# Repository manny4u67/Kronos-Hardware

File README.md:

# Kronos Hardware
 Kronos - By AddeyX

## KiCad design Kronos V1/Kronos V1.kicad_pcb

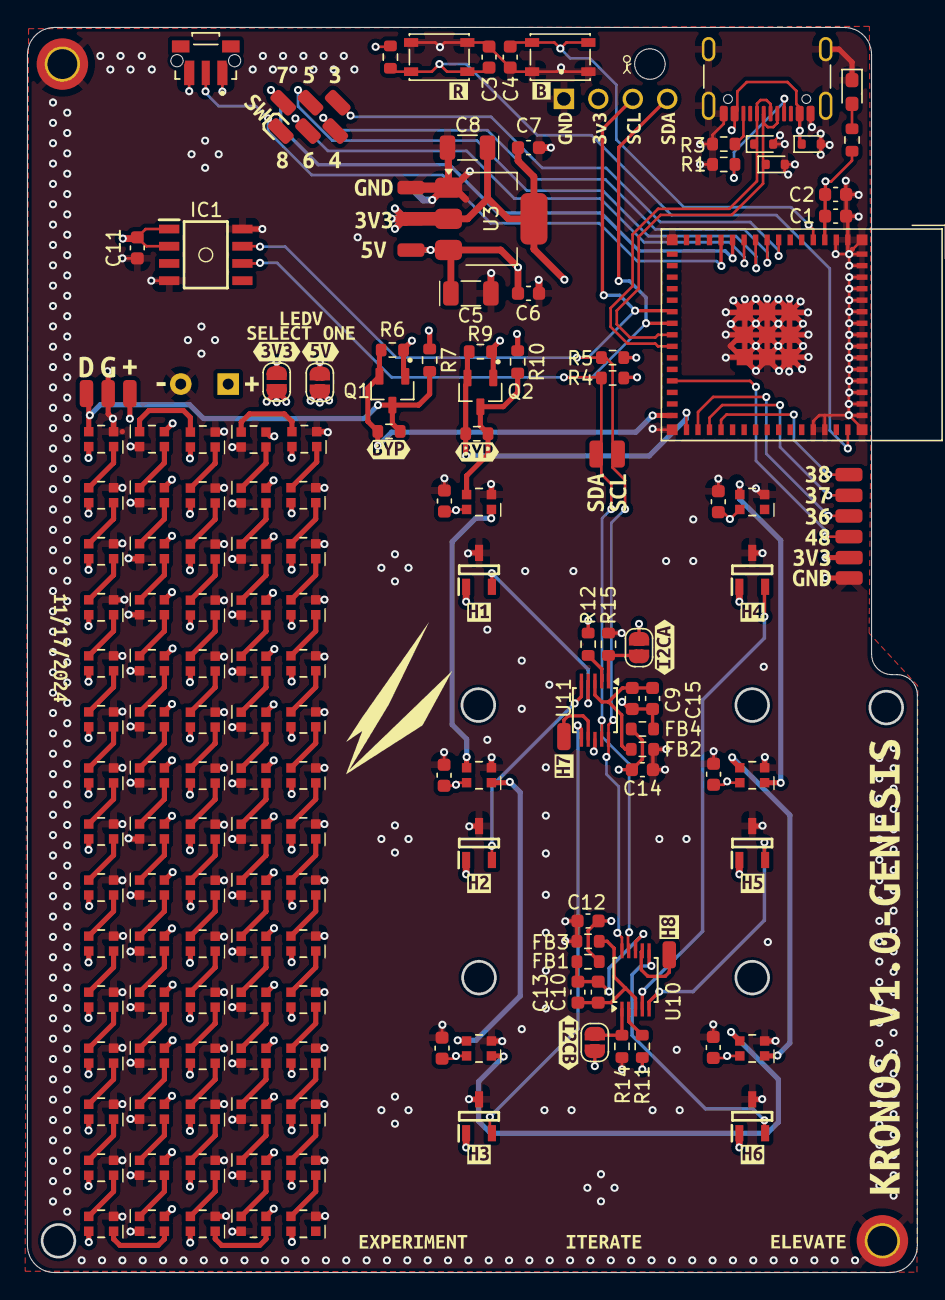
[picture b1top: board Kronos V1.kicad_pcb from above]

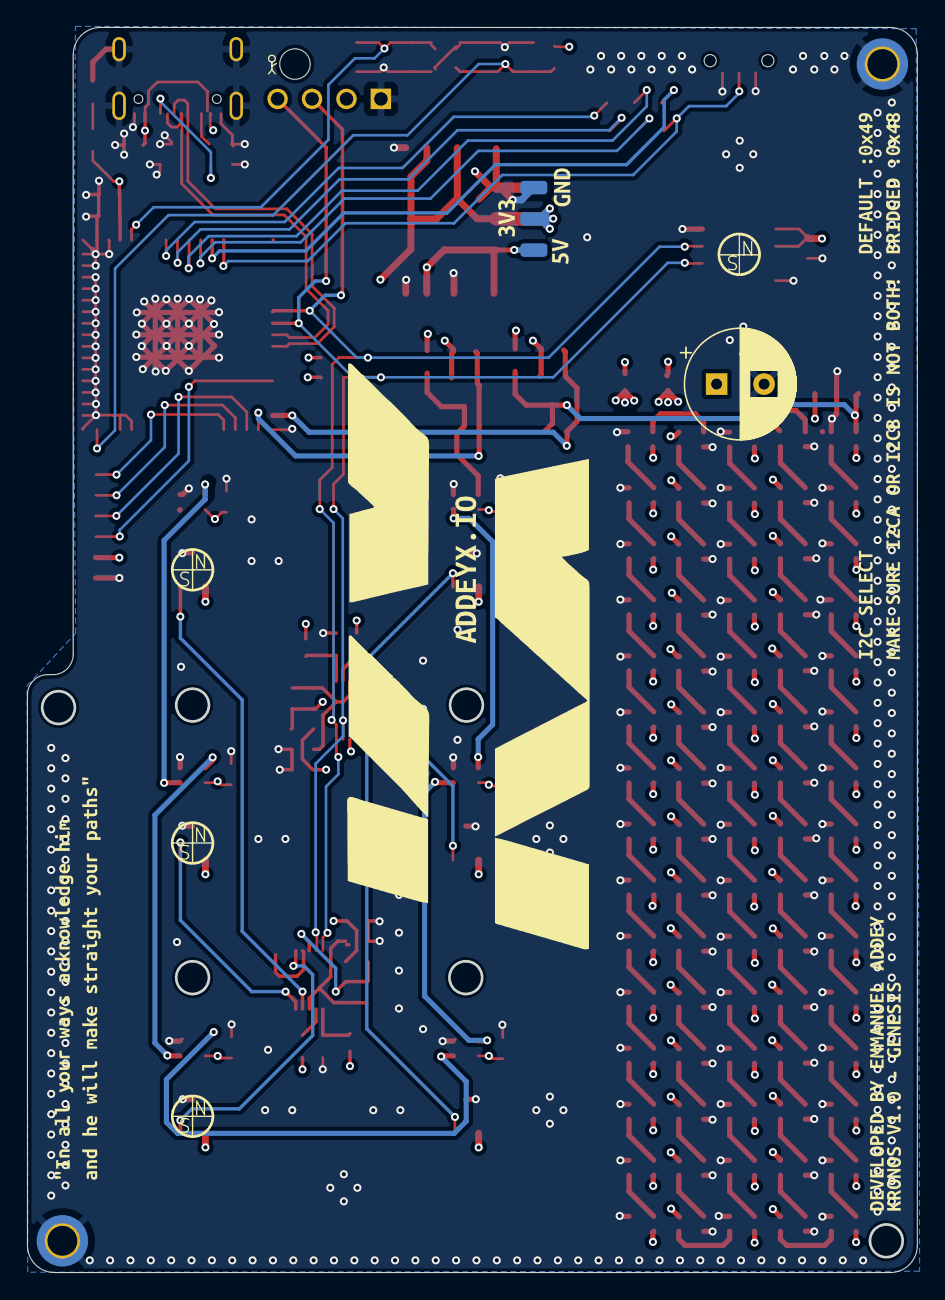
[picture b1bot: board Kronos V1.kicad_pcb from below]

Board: 4 copper layers, 65.6 x 91.8 mm, 229 parts (12 on the bottom side), 122 nets.

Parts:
BOOT1: SW_SPST_PTS810
C1, C3, C4, C92, C93, C94, C95, C96, C97: 0.1uF; C_0603_1608Metric
C2, C9, C10, C12, C14: 10uF; C_0603_1608Metric
C5, C8: 22uF; C_1206_3216Metric
C6, C7, C11, C13, C15: 100nf; C_0603_1608Metric
C17: C_Polarized_US; CP_Radial_D8.0mm_P3.50mm
D1, D2, D3: TPD1E10B06; D_SOD-523
D4: LED; LED_0603_1608Metric_Pad1.05x0.95mm_HandSolder
FB1, FB2, FB3, FB4: FerriteBead_Small; R_0603_1608Metric
H1, H2: MountingHole_Pad; MountingHole_2.2mm_M2_DIN965_Pad_TopBottom
IC1: AS5600-ASOT; AS5600_SOIC127P600X175-8N
J1: USB_C_Receptacle_USB2.0_16P; USB_C_Receptacle_GCT_USB4105-xx-A_16P_TopMnt_Horizontal
JP1, JP2, JP3, JP4: SolderJumper_2_Open; SolderJumper-2_P1.3mm_Open_RoundedPad1.0x1.5mm
PD1, PD2, PD3, PD4, PD5, PD6, PD7, PD8, PD9, PD10, PD11, PD12, PD13, PD13#2, PD14, PD14#2, PD14#3, PD14#4, PD15, PD15#2, PD17, PD18, PD19, PD20, PD21: Test_Pad2
Q1, Q2: BSS138; SOT95P240X111-3N
R1, R3, R16: 5.1k; R_0603_1608Metric
R2, R4, R5, R6, R7, R9, R10, R11, R12, R14, R15: 10k; R_0603_1608Metric
R8, R13: 0(JMP); R_0603_1608Metric
RESET1: SW_SPST_PTS810
S1: TL3340AF160QG; SW_TL3340AF160QG
U1: DM-OLED096-636; MODULE_DM-OLED096-636
U2: ESP32-S3-MINI-1; ESP32-S2-MINI-1
U3: AMS1117-3.3; SOT-223-3_TabPin2
U4, U5, U6, U7, U8, U9: AH49ENTR-G1; SOT95P280X145-3N
U10, U11: ADS1115IDGS; TSSOP-10_3x3mm_P0.5mm
U12, U13, U14, U15, U16, U17, U18, U19, U20, U21, U22, U23, U24, U25, U26, U27, U28, U29, U30, U31, U32, U33, U34, U35, U36, U37, U38, U39, U40, U41, U42, U43, U44, U45, U46, U47, U48, U49, U50, U51, U52, U53, U54, U55, U56, U57, U58, U59, U60, U61, U62, U63, U64, U65, U66, U67, U68, U69, U70, U71, U72, U73, U74, U75, U76, U77, U78, U79, U80, U81, U82, U83, U84, U85, U86, U87, U88, U89, U90, U91, U92: WS2812-2020; LED_WS2812-2020
kibuzzard-66F4CFAA: G***; kibuzzard-66F4CFAA
kibuzzard-66FB33A5: G***; kibuzzard-66FB33A5
kibuzzard-66FB339E: G***; kibuzzard-66FB339E
kibuzzard-66FB3378: G***; kibuzzard-66FB3378
kibuzzard-66FCA7D9: G***; kibuzzard-66FCA7D9
kibuzzard-66FCA7E8: G***; kibuzzard-66FCA7E8
kibuzzard-673A4A14: G***; kibuzzard-673A4A14
kibuzzard-673A4A24: G***; kibuzzard-673A4A24
kibuzzard-673A6C08: G***; kibuzzard-673A6C08
kibuzzard-673A37E5: G***; kibuzzard-673A37E5
kibuzzard-673A37ED: G***; kibuzzard-673A37ED
kibuzzard-673A37F5: G***; kibuzzard-673A37F5
kibuzzard-673A52CF: G***; kibuzzard-673A52CF
kibuzzard-673A66C9: G***; kibuzzard-673A66C9
kibuzzard-673A66CE: G***; kibuzzard-673A66CE
kibuzzard-673A66D4: G***; kibuzzard-673A66D4
kibuzzard-673A66D9: G***; kibuzzard-673A66D9
kibuzzard-673A67D1: G***; kibuzzard-673A67D1
kibuzzard-673A367D, kibuzzard-673A367D#2: G***; kibuzzard-673A367D
kibuzzard-673A380C: G***; kibuzzard-673A380C
kibuzzard-673A2861: G***; kibuzzard-673A2861
kibuzzard-673A2872: G***; kibuzzard-673A2872
kibuzzard-673A3813: G***; kibuzzard-673A3813
kibuzzard-673A3819: G***; kibuzzard-673A3819
kibuzzard-673A4853: G***; kibuzzard-673A4853
kibuzzard-673AB92A: G***; kibuzzard-673AB92A
kibuzzard-673BD2C0: G***; kibuzzard-673BD2C0
kibuzzard-673BD08D: G***; kibuzzard-673BD08D
kibuzzard-673BD012: G***; kibuzzard-673BD012
kibuzzard-673BD17F: G***; kibuzzard-673BD17F
kibuzzard-673BD057: G***; kibuzzard-673BD057
kibuzzard-673BDAC6: G***; kibuzzard-673BDAC6
kibuzzard-6736A45D: G***; kibuzzard-6736A45D
kibuzzard-6736A453: G***; kibuzzard-6736A453
kibuzzard-6736AEA1: G***; kibuzzard-6736AEA1
kibuzzard-6736AEA5: G***; kibuzzard-6736AEA5
kibuzzard-6736AEAD: G***; kibuzzard-6736AEAD
kibuzzard-6736AEB1: G***; kibuzzard-6736AEB1
kibuzzard-6736AEBA, kibuzzard-6736AEBA#2, kibuzzard-6736AEBA#3: G***; kibuzzard-6736AEBA
kibuzzard-6736AEC3, kibuzzard-6736AEC3#2, kibuzzard-6736AEC3#3: G***; kibuzzard-6736AEC3
kibuzzard-67368FCC: G***; kibuzzard-67368FCC
kibuzzard-67368FDA: G***; kibuzzard-67368FDA
kibuzzard-673412D5: G***; kibuzzard-673412D5
kibuzzard-673412DD: G***; kibuzzard-673412DD
kibuzzard-66993841: G***; kibuzzard-66993841
kibuzzard-67341636: G***; kibuzzard-67341636
kibuzzard-67341641: G***; kibuzzard-67341641
kibuzzard-67341688: G***; kibuzzard-67341688

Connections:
3V3: C1.1, C2.1, C7.1, C8.1, C11.2, C12.2, C14.2, FB1.1, FB2.1, IC1.1 (VDD5V), IC1.2 (VDD3V3), JP1.1 (A), JP2.1 (A), JP4.2 (B), PD12.1, PD14#3.1, PD14#4.1, Q1.1, Q2.1, R2.1, R4.1, R5.1, R6.1, R9.1, R11.1, R12.1, R16.2, U1.2 (VCC_IN), U2.3 (3V3), U3.2 (VO), U4.1 (VCC), U5.1 (VCC), U6.1 (VCC), U7.1 (VCC), U8.1 (VCC), U9.1 (VCC)
5VUSB: C5.1, C6.2, D1.1 (A1), J1.A4 (VBUS), J1.A9 (VBUS), J1.B4 (VBUS), J1.B9 (VBUS), JP3.1 (A), PD13.1, PD13#2.1, R7.1, R10.1, U3.3 (VI)
/ESP32_EN: C3.1, R2.2, RESET1.3 (K), RESET1.4 (A), U2.45 (EN)
/GPIO0: BOOT1.3 (K), BOOT1.4 (A), C4.1, U2.4 (IO0)
/GPIO3: PD1.1, U2.7 (IO3)
/GPIO4: PD2.1, U2.8 (IO4)
/GPIO5: PD3.1, U2.9 (IO5)
/GPIO6: PD4.1, U2.10 (IO6)
/GPIO7: PD5.1, U2.11 (IO7)
/GPIO8: PD6.1, S1.2, U2.12 (IO8)
/GPIO36: PD7.1, U2.32 (IO36)
/GPIO37: PD8.1, U2.33 (IO37)
/GPIO38: PD9.1, U2.34 (IO38)
/GPIO47: PD10.1, U2.27 (IO47)
/HALLC1R1: U5.2 (OUT), U10.4 (AIN0)
/HALLC1R2: U6.2 (OUT), U10.5 (AIN1)
/HALLC1R3: U8.2 (OUT), U10.6 (AIN2)
/HALLC2R1: U4.2 (OUT), U11.4 (AIN0)
/HALLC2R2: U7.2 (OUT), U11.5 (AIN1)
/HALLC2R3: U9.2 (OUT), U11.6 (AIN2)
/I2C_SCL: IC1.7 (SCL), PD14.1, R5.2, U1.3 (SCL), U2.21 (IO17), U10.10 (SCL), U11.10 (SCL)
/I2C_SDA: IC1.6 (SDA), PD14#2.1, R4.2, U1.4 (SDA), U2.22 (IO18), U10.9 (SDA), U11.9 (SDA)
/USB_N: D3.1 (A1), J1.A7 (D-), J1.B7 (D-), U2.23 (IO19)
/USB_P: D2.1 (A1), J1.A6 (D+), J1.B6 (D+), U2.24 (IO20)
A3V3: C10.2, C13.2, FB1.2, U10.8 (VDD)
A3V3B: C9.2, C15.2, FB2.2, U11.8 (VDD)
AGND: C10.1, C13.1, FB3.2, U10.3 (GND)
AGNDB: C9.1, C15.1, FB4.2, U11.3 (GND)
AUXRGBOUT: PD20.1, Q1.3, R7.2, R8.1, U12.3 (DI)
GND: BOOT1.1, BOOT1.2, C1.2, C2.2, C3.2, C4.2, C5.2, C6.1, C7.2, C8.2, C11.1, C12.1, C14.1, C17.2, C92.2, C93.2, C94.2, C95.2, C96.2, C97.2, D1.2 (A2), D2.2 (A2), D3.2 (A2), D4.1, FB3.1, FB4.1, H1.1, H2.1, IC1.4 (GND), IC1.8 (DIR), J1.A1 (GND), J1.A12 (GND), J1.B1 (GND), J1.B12 (GND), J1.S1 (SHIELD), PD11.1, PD15.1, PD15#2.1, PD21.1, R1.2, R3.2, R14.2, R15.2, RESET1.1, RESET1.2, S1.1, S1.3, U1.1 (GND), U2.1 (GND), U2.2 (GND), U2.42 (GND), U2.43 (GND), U2.46 (GND), U2.47 (GND), U2.48 (GND), U2.49 (GND), U2.50 (GND), U2.51 (GND), U2.52 (GND), U2.53 (GND), U2.54 (GND), U2.55 (GND), U2.56 (GND), U2.57 (GND), U2.58 (GND), U2.59 (GND), U2.60 (GND), U2.61 (GND), U2.62 (GND), U2.63 (GND), U2.64 (GND), U2.65 (GND), U3.1 (GND), U4.3 (GND), U5.3 (GND), U6.3 (GND), U7.3 (GND), U8.3 (GND), U9.3 (GND), U12.2 (GND), U13.2 (GND), U14.2 (GND), U15.2 (GND), U16.2 (GND), U17.2 (GND), U18.2 (GND), U19.2 (GND), U20.2 (GND), U21.2 (GND), U22.2 (GND), U23.2 (GND), U24.2 (GND), U25.2 (GND), U26.2 (GND), U27.2 (GND), U28.2 (GND), U29.2 (GND), U30.2 (GND), U31.2 (GND), U32.2 (GND), U33.2 (GND), U34.2 (GND), U35.2 (GND), U36.2 (GND), U37.2 (GND), U38.2 (GND), U39.2 (GND), U40.2 (GND), U41.2 (GND), U42.2 (GND), U43.2 (GND), U44.2 (GND), U45.2 (GND), U46.2 (GND), U47.2 (GND), U48.2 (GND), U49.2 (GND), U50.2 (GND), U51.2 (GND), U52.2 (GND), U53.2 (GND), U54.2 (GND), U55.2 (GND), U56.2 (GND), U57.2 (GND), U58.2 (GND), U59.2 (GND), U60.2 (GND), U61.2 (GND), U62.2 (GND), U63.2 (GND), U64.2 (GND), U65.2 (GND), U66.2 (GND), U67.2 (GND), U68.2 (GND), U69.2 (GND), U70.2 (GND), U71.2 (GND), U72.2 (GND), U73.2 (GND), U74.2 (GND), U75.2 (GND), U76.2 (GND), U77.2 (GND), U78.2 (GND), U79.2 (GND), U80.2 (GND), U81.2 (GND), U82.2 (GND), U83.2 (GND), U84.2 (GND), U85.2 (GND), U86.2 (GND), U87.2 (GND), U88.2 (GND), U89.2 (GND), U90.2 (GND), U91.2 (GND), U92.2 (GND)
GPIO35: Q2.2, R9.2, R13.2, U2.31 (IO35)
GPIO48: Q1.2, R6.2, R8.2, U2.30 (IO48)
LEDVSEL: C17.1, C92.1, C93.1, C94.1, C95.1, C96.1, C97.1, JP3.2 (B), JP4.1 (A), PD19.1, U12.4 (VDD), U13.4 (VDD), U14.4 (VDD), U15.4 (VDD), U16.4 (VDD), U17.4 (VDD), U18.4 (VDD), U19.4 (VDD), U20.4 (VDD), U21.4 (VDD), U22.4 (VDD), U23.4 (VDD), U24.4 (VDD), U25.4 (VDD), U26.4 (VDD), U27.4 (VDD), U28.4 (VDD), U29.4 (VDD), U30.4 (VDD), U31.4 (VDD), U32.4 (VDD), U33.4 (VDD), U34.4 (VDD), U35.4 (VDD), U36.4 (VDD), U37.4 (VDD), U38.4 (VDD), U39.4 (VDD), U40.4 (VDD), U41.4 (VDD), U42.4 (VDD), U43.4 (VDD), U44.4 (VDD), U45.4 (VDD), U46.4 (VDD), U47.4 (VDD), U48.4 (VDD), U49.4 (VDD), U50.4 (VDD), U51.4 (VDD), U52.4 (VDD), U53.4 (VDD), U54.4 (VDD), U55.4 (VDD), U56.4 (VDD), U57.4 (VDD), U58.4 (VDD), U59.4 (VDD), U60.4 (VDD), U61.4 (VDD), U62.4 (VDD), U63.4 (VDD), U64.4 (VDD), U65.4 (VDD), U66.4 (VDD), U67.4 (VDD), U68.4 (VDD), U69.4 (VDD), U70.4 (VDD), U71.4 (VDD), U72.4 (VDD), U73.4 (VDD), U74.4 (VDD), U75.4 (VDD), U76.4 (VDD), U77.4 (VDD), U78.4 (VDD), U79.4 (VDD), U80.4 (VDD), U81.4 (VDD), U82.4 (VDD), U83.4 (VDD), U84.4 (VDD), U85.4 (VDD), U86.4 (VDD), U87.4 (VDD), U88.4 (VDD), U89.4 (VDD), U90.4 (VDD), U91.4 (VDD), U92.4 (VDD)
unnamed: D4.2, R16.1
unnamed: J1.A5 (CC1), R1.1
unnamed: J1.B5 (CC2), R3.1
unnamed: JP1.2 (B), R14.1, U10.1 (ADDR)
unnamed: JP2.2 (B), R15.1, U11.1 (ADDR)
unnamed: PD17.1, U10.7 (AIN3)
unnamed: R11.2, U10.2 (ALERT/RDY)
unnamed: PD18.1, U11.7 (AIN3)
unnamed: R12.2, U11.2 (ALERT/RDY)
unnamed: U12.1 (DO), U13.3 (DI)
unnamed: U13.1 (DO), U14.3 (DI)
unnamed: U14.1 (DO), U15.3 (DI)
unnamed: U15.1 (DO), U16.3 (DI)
unnamed: U16.1 (DO), U17.3 (DI)
unnamed: U17.1 (DO), U18.3 (DI)
unnamed: U18.1 (DO), U19.3 (DI)
unnamed: U19.1 (DO), U20.3 (DI)
unnamed: U20.1 (DO), U21.3 (DI)
unnamed: U21.1 (DO), U22.3 (DI)
unnamed: U22.1 (DO), U23.3 (DI)
unnamed: U23.1 (DO), U24.3 (DI)
unnamed: U24.1 (DO), U25.3 (DI)
unnamed: U25.1 (DO), U26.3 (DI)
unnamed: U26.1 (DO), U27.3 (DI)
unnamed: U27.1 (DO), U28.3 (DI)
unnamed: U28.1 (DO), U29.3 (DI)
unnamed: U29.1 (DO), U30.3 (DI)
unnamed: U30.1 (DO), U31.3 (DI)
unnamed: U31.1 (DO), U32.3 (DI)
unnamed: U32.1 (DO), U33.3 (DI)
unnamed: U33.1 (DO), U34.3 (DI)
unnamed: U34.1 (DO), U35.3 (DI)
unnamed: U35.1 (DO), U36.3 (DI)
unnamed: U36.1 (DO), U37.3 (DI)
unnamed: U37.1 (DO), U38.3 (DI)
unnamed: U38.1 (DO), U39.3 (DI)
unnamed: U39.1 (DO), U40.3 (DI)
unnamed: U40.1 (DO), U41.3 (DI)
unnamed: U41.1 (DO), U42.3 (DI)
unnamed: U42.1 (DO), U43.3 (DI)
unnamed: U43.1 (DO), U44.3 (DI)
unnamed: U44.1 (DO), U45.3 (DI)
unnamed: U45.1 (DO), U46.3 (DI)
unnamed: U46.1 (DO), U47.3 (DI)
unnamed: U47.1 (DO), U48.3 (DI)
unnamed: U48.1 (DO), U49.3 (DI)
unnamed: U49.1 (DO), U50.3 (DI)
unnamed: U50.1 (DO), U51.3 (DI)
unnamed: U51.1 (DO), U52.3 (DI)
unnamed: U52.1 (DO), U53.3 (DI)
unnamed: U53.1 (DO), U54.3 (DI)
unnamed: U54.1 (DO), U55.3 (DI)
unnamed: U55.1 (DO), U56.3 (DI)
unnamed: U56.1 (DO), U57.3 (DI)
unnamed: U57.1 (DO), U58.3 (DI)
unnamed: U58.1 (DO), U59.3 (DI)
unnamed: U59.1 (DO), U60.3 (DI)
unnamed: U60.1 (DO), U61.3 (DI)
unnamed: U61.1 (DO), U62.3 (DI)
unnamed: U62.1 (DO), U63.3 (DI)
unnamed: U63.1 (DO), U64.3 (DI)
unnamed: U64.1 (DO), U65.3 (DI)
unnamed: U65.1 (DO), U66.3 (DI)
unnamed: U66.1 (DO), U67.3 (DI)
unnamed: U67.1 (DO), U68.3 (DI)
unnamed: U68.1 (DO), U69.3 (DI)
unnamed: U69.1 (DO), U70.3 (DI)
unnamed: U70.1 (DO), U71.3 (DI)
unnamed: U71.1 (DO), U72.3 (DI)
unnamed: U72.1 (DO), U73.3 (DI)
unnamed: U73.1 (DO), U74.3 (DI)
unnamed: U74.1 (DO), U75.3 (DI)
unnamed: U75.1 (DO), U76.3 (DI)
unnamed: U76.1 (DO), U77.3 (DI)
unnamed: U77.1 (DO), U78.3 (DI)
unnamed: U78.1 (DO), U79.3 (DI)
unnamed: U79.1 (DO), U80.3 (DI)
unnamed: U80.1 (DO), U81.3 (DI)
unnamed: U81.1 (DO), U82.3 (DI)
unnamed: U82.1 (DO), U83.3 (DI)
unnamed: U83.1 (DO), U84.3 (DI)
unnamed: U84.1 (DO), U85.3 (DI)
unnamed: U85.1 (DO), U86.3 (DI)
unnamed: U87.1 (DO), U88.3 (DI)
unnamed: U88.1 (DO), U89.3 (DI)
unnamed: U89.1 (DO), U90.3 (DI)
unnamed: U90.1 (DO), U91.3 (DI)
unnamed: U91.1 (DO), U92.3 (DI)
OBRGB OUT: Q2.3, R10.2, R13.1, U87.3 (DI)

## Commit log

2024-12-06 Uploading KiCad Files
2024-12-06 Update fp-info-cache
2024-12-06 Added 3D files
2024-12-11 Solidworks temp filez
2024-12-11 Corrected error with H4 ARGB
2024-12-12 Completed rotary encoder portion
2024-12-27 Complete Design For MacroPad
    Need to rename some parts to make it more understandable
2024-12-31 Added Test Firmware
2025-04-02 Hardware
